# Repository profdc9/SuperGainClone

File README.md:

# Stereo Super Gain Clone layout

This is a two-channel PCB layout for the LM3886-based Super Gain Clone by Bob Cordell.  It can be found in Chapter 27 in his book "Audio Amplifiers."

This project layout separates signal and power grounds as specified in the schematic.  It is intended to be a compact layout that will fit in a small amplifier case.  The two input ground should be joined where they enter the chassis, as they are not joined on the PCB except for hum breakers resistors.  The PCB is made available under the Creative Commons CC-BY-SA 4.0 license.

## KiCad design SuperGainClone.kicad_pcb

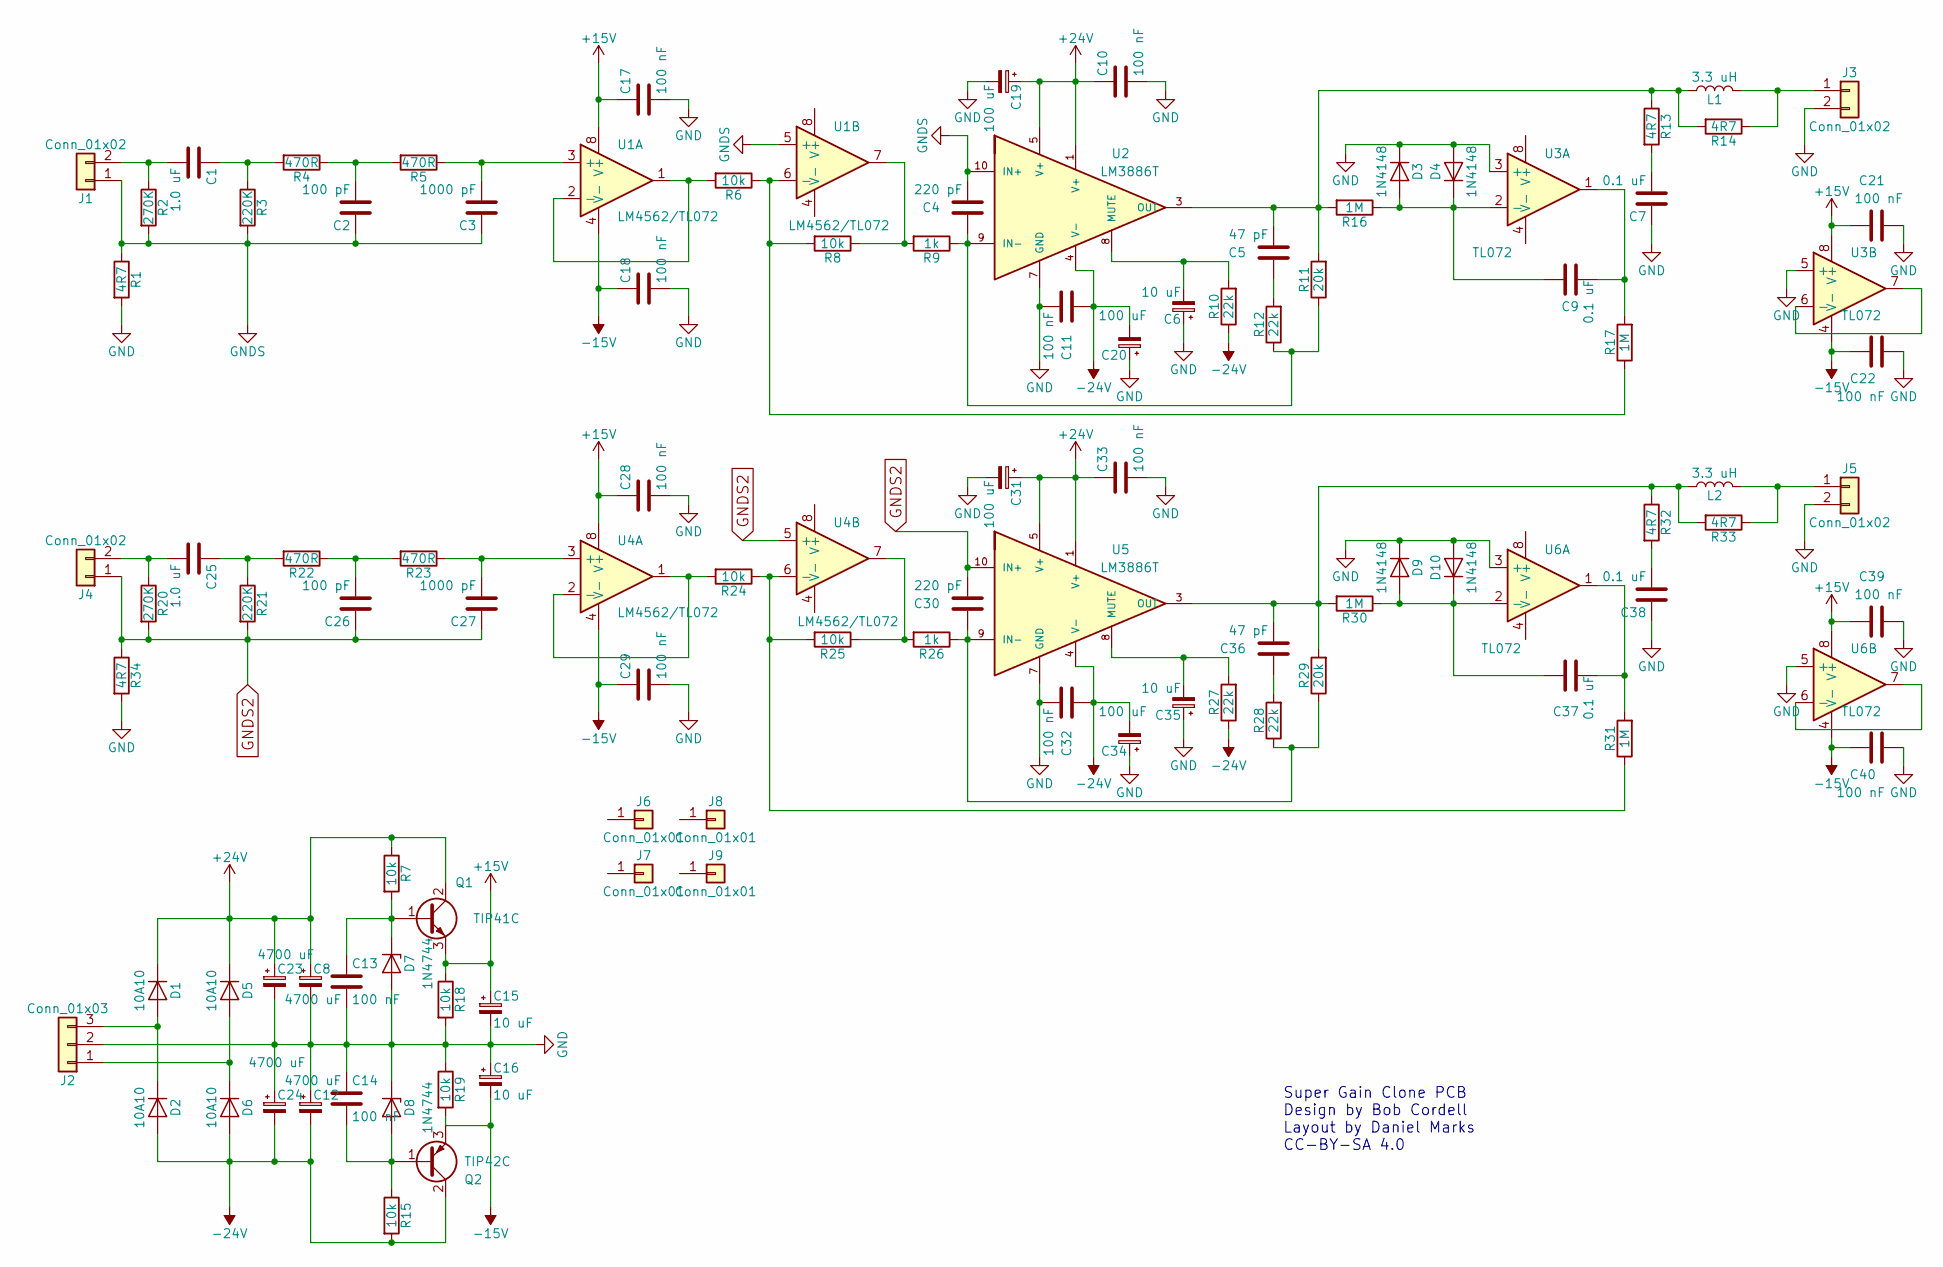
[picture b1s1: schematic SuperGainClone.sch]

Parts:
C1, C25: 1.0 uF; C_Rect_L11.5mm_W5.0mm_P10.00mm_MKT
C2, C26: 100 pF; C_Disc_D5.0mm_W2.5mm_P5.00mm
C3, C27: 1000 pF; C_Disc_D5.0mm_W2.5mm_P5.00mm
C4, C30: 220 pF; C_Disc_D5.0mm_W2.5mm_P5.00mm
C5, C36: 47 pF; C_Disc_D5.0mm_W2.5mm_P5.00mm
C6, C15, C16, C35: 10 uF; CP_Radial_D7.5mm_P2.50mm
C7, C9, C37, C38: 0.1 uF; C_Axial_L5.1mm_D3.1mm_P10.00mm_Horizontal
C8, C12, C23, C24: 4700 uF; CP_Radial_D18.0mm_P7.50mm
C10, C11, C13, C14, C17, C18, C21, C22, C28, C29, C32, C33, C39, C40: 100 nF; C_Disc_D5.0mm_W2.5mm_P5.00mm
C19, C20, C31, C34: 100 uF; CP_Radial_D10.0mm_P3.50mm
D1, D2, D5, D6: 10A10; D_5KPW_P12.70mm_Horizontal
D3, D4, D9, D10: 1N4148; D_DO-35_SOD27_P7.62mm_Horizontal
D7, D8: 1N4744; D_DO-41_SOD81_P7.62mm_Horizontal
J1, J3, J4, J5: Conn_01x02; TerminalBlock_bornier-2_P5.08mm
J2: Conn_01x03; TerminalBlock_bornier-3_P5.08mm
J6, J7, J8, J9: Conn_01x01; 1pin
L1, L2: 3.3 uH; L_Radial_D14.2mm_P10.00mm_Neosid_SD14
Q1: TIP41C; TO-220-3_Vertical
Q2: TIP42C; TO-220-3_Vertical
R1, R34: 4R7; R_Axial_DIN0207_L6.3mm_D2.5mm_P7.62mm_Horizontal
R2, R20: 270K; R_Axial_DIN0207_L6.3mm_D2.5mm_P7.62mm_Horizontal
R3, R21: 220K; R_Axial_DIN0207_L6.3mm_D2.5mm_P7.62mm_Horizontal
R4, R5, R22, R23: 470R; R_Axial_DIN0207_L6.3mm_D2.5mm_P7.62mm_Horizontal
R6, R8, R24, R25: 10k; R_Axial_DIN0207_L6.3mm_D2.5mm_P7.62mm_Horizontal
R7, R15, R18, R19: 10k; R_Axial_DIN0411_L9.9mm_D3.6mm_P12.70mm_Horizontal
R9, R26: 1k; R_Axial_DIN0207_L6.3mm_D2.5mm_P7.62mm_Horizontal
R10, R12, R27, R28: 22k; R_Axial_DIN0207_L6.3mm_D2.5mm_P7.62mm_Horizontal
R11, R29: 20k; R_Axial_DIN0207_L6.3mm_D2.5mm_P7.62mm_Horizontal
R13, R14, R32, R33: 4R7; R_Axial_DIN0411_L9.9mm_D3.6mm_P12.70mm_Horizontal
R16, R17, R30, R31: 1M; R_Axial_DIN0207_L6.3mm_D2.5mm_P7.62mm_Horizontal
U1, U4: LM4562/TL072; DIP-8_W7.62mm_Socket
U2, U5: LM3886T; TO-220-11_Vertical_StaggeredType1
U3, U6: TL072; DIP-8_W7.62mm_Socket

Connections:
+15V: C15.1, C17.1, C21.1, C28.1, C39.1, Q1.3 (E), R18.1, U1.8 (V+), U3.8 (V+), U4.8 (V+), U6.8 (V+)
+24V: C8.1, C10.1, C19.1, C23.1, C31.1, C33.1, D1.1 (K), D5.1 (K), Q1.2 (C), R7.1, U2.1 (V+), U2.5 (V+), U5.1 (V+), U5.5 (V+)
-15V: C16.2, C18.1, C22.1, C29.1, C40.1, Q2.3 (E), R19.2, U1.4 (V-), U3.4 (V-), U4.4 (V-), U6.4 (V-)
-24V: C11.1, C12.2, C20.2, C24.2, C32.1, C34.2, D2.2 (A), D6.2 (A), Q2.2 (C), R10.1, R15.2, R27.1, U2.4 (V-), U5.4 (V-)
GND: C6.1, C7.1, C8.2, C10.2, C11.2, C12.1, C13.2, C14.1, C15.2, C16.1, C17.2, C18.2, C19.2, C20.1, C21.2, C22.2, C23.2, C24.1, C28.2, C29.2, C31.2, C32.2, C33.2, C34.1, C35.1, C38.1, C39.2, C40.2, D3.1 (K), D4.2 (A), D7.2 (A), D8.1 (K), D9.1 (K), D10.2 (A), J2.2, J3.2, J5.2, R1.2, R18.2, R19.1, R34.2, U2.7 (GND), U3.3 (+), U3.5 (+), U5.7 (GND), U6.3 (+), U6.5 (+)
GNDS: C2.1, C3.1, C4.2, J1.1, R1.1, R2.2, R3.2, U1.5 (+), U2.10 (IN+)
GNDS2: C26.1, C27.1, C30.2, J4.1, R20.2, R21.2, R34.1, U4.5 (+), U5.10 (IN+)
unnamed: C1.1, R3.1, R4.2
unnamed: C1.2, J1.2, R2.1
unnamed: C2.2, R4.1, R5.2
unnamed: C3.2, R5.1, U1.3 (+)
unnamed: C4.1, R9.1, R11.1, R12.1, U2.9 (IN-)
unnamed: C5.1, R12.2
unnamed: C5.2, L1.1, R11.2, R13.1, R14.2, R16.2, U2.3 (OUT)
unnamed: C6.2, R10.2, U2.8 (MUTE)
unnamed: C7.2, R13.2
unnamed: C9.1, D3.2 (A), D4.1 (K), R16.1, U3.2 (-)
unnamed: C9.2, R17.2, U3.1
unnamed: C13.1, D7.1 (K), Q1.1 (B), R7.2
unnamed: C14.2, D8.2 (A), Q2.1 (B), R15.1
unnamed: C25.1, R21.1, R22.2
unnamed: C25.2, J4.2, R20.1
unnamed: C26.2, R22.1, R23.2
unnamed: C27.2, R23.1, U4.3 (+)
unnamed: C30.1, R26.1, R28.1, R29.1, U5.9 (IN-)
unnamed: C35.2, R27.2, U5.8 (MUTE)
unnamed: C36.1, R28.2
unnamed: C36.2, L2.1, R29.2, R30.2, R32.1, R33.2, U5.3 (OUT)
unnamed: C37.1, D9.2 (A), D10.1 (K), R30.1, U6.2 (-)
unnamed: C37.2, R31.2, U6.1
unnamed: C38.2, R32.2
unnamed: D1.2 (A), D2.1 (K), J2.3
unnamed: D5.2 (A), D6.1 (K), J2.1
unnamed: J3.1, L1.2, R14.1
unnamed: J5.1, L2.2, R33.1
unnamed: R6.2, U1.1, U1.2 (-)
unnamed: R8.1, R9.2, U1.7
unnamed: R6.1, R8.2, R17.1, U1.6 (-)
unnamed: R24.1, R25.2, R31.1, U4.6 (-)
unnamed: R24.2, U4.1, U4.2 (-)
unnamed: R25.1, R26.2, U4.7
unnamed: U3.6 (-), U3.7
unnamed: U6.6 (-), U6.7

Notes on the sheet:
Super Gain Clone PCB Design by Bob Cordell Layout by Daniel Marks CC-BY-SA 4.0

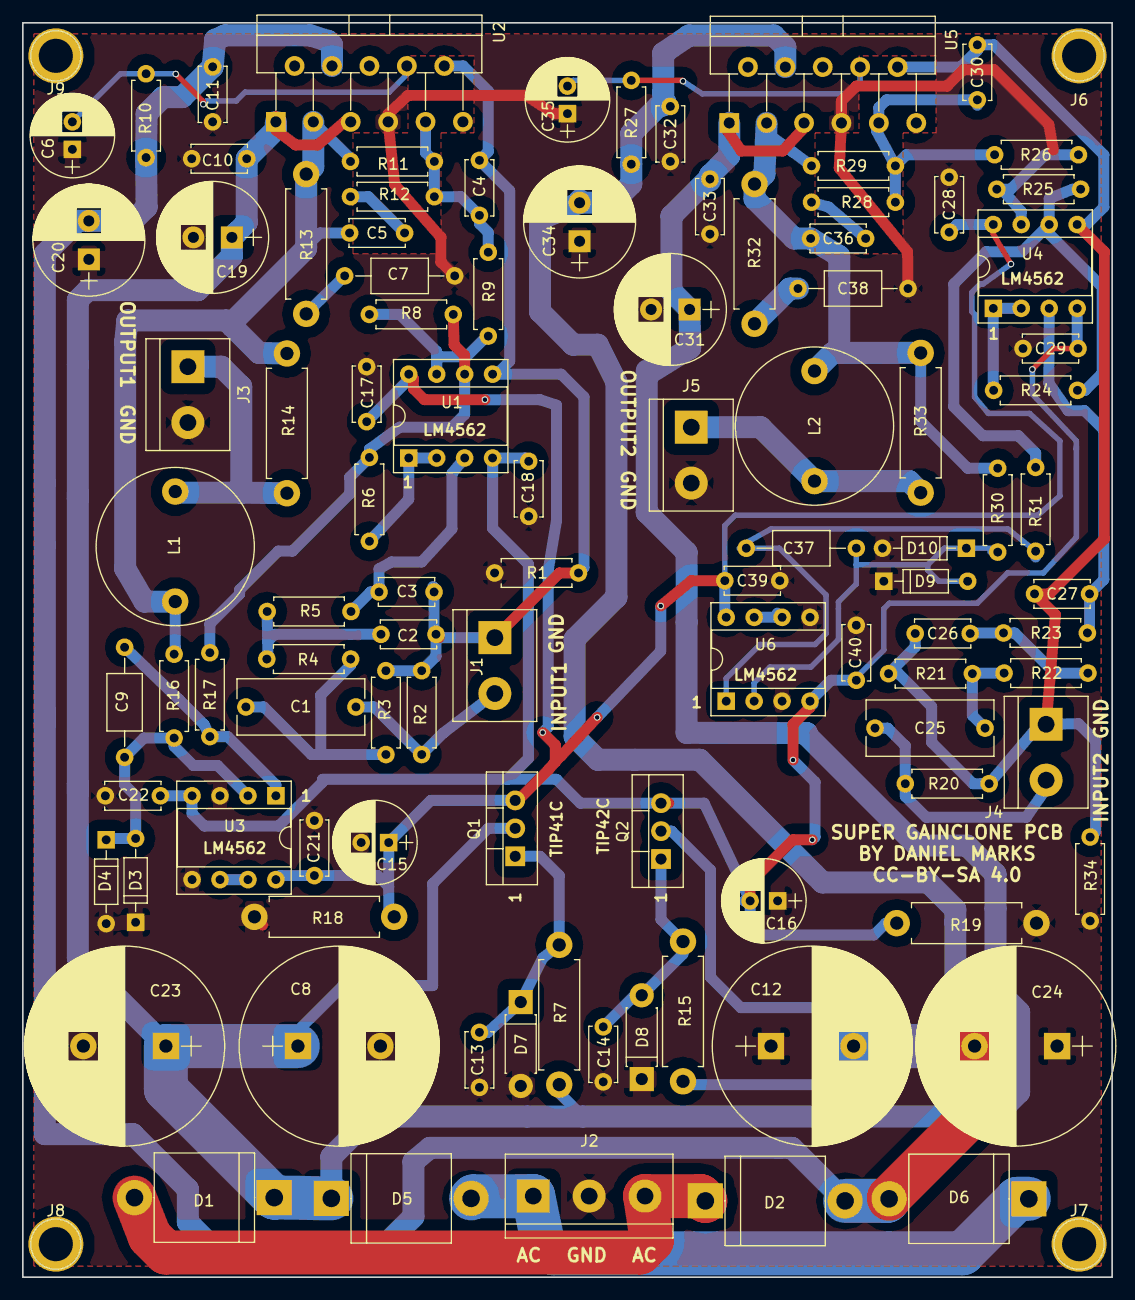
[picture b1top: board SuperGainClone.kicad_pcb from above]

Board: 2 copper layers, 99.0 x 114.0 mm, 103 parts (0 on the bottom side), 43 nets.

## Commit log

2020-10-29 Rearranged some components
2020-11-19 Fixed DC servo feedback
